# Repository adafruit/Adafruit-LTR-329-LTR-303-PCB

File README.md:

## Adafruit LTR-329 and LTR-303 Light Sensor PCBs

<a href="http://www.adafruit.com/products/5591"><br/>
Click here to purchase one from the Adafruit shop</a>

<a href="http://www.adafruit.com/products/5610"><br/>
Click here to purchase one from the Adafruit shop</a>

PCB files for the Adafruit LTR-329 and LTR-303 Light Sensor. 

Format is EagleCAD schematic and board layout
* https://www.adafruit.com/product/5591
* https://www.adafruit.com/product/5610

### Description

The Adafruit LTR-303 and LTR-329 Light Sensors are simple and popular low-cost I2C digital light sensors that are easy to integrate into your project for reliable and wide-ranging light measurements.

Perfect for a wide range of project use cases: Should we turn up the brightness of our display or dim it to save power? Which direction should your robot move to stay in an area with the most light? Is it day or night? All of these questions can be answered with the help of the LTR-303 and LTR-329. They're small, capable and inexpensive light sensors that you can include in your next project to add the detection and measurement of light.

They provide 16-bit light measurements for both Infrared and Visible+IR spectrums. Subtract one from the other to get human-visible light. Thanks to configurable gain and integration time settings, the LTR-303 can measure from 0 to 65K+ lux.

The 303 also comes with alert and IRQ capabilities so you can have a pin trigger when the reading goes above or below threshold values. Great if you want ultra-low power usage. If you don't need a version with interrupt output, check out the LTR-329 which is basically the same sensor but without the IRQ capability.

Packaged on a PCB in our STEMMA QT form factor, the LTR-303 comes integrated with a voltage regulator and level shifting circuitry to allow it to be used with 3.3V devices, like a Feather M4 or Raspberry Pi, or 5V devices, such as an Arduino. Rather than working with the itty bitty little contacts on the sensor, the PCB it's packaged on breaks out all the pins to a standard 0.1" / 2.54mm pitch header.

### License

Adafruit invests time and resources providing this open source design, please support Adafruit and open-source hardware by purchasing products from [Adafruit](https://www.adafruit.com)!

Designed by Limor Fried/Ladyada for Adafruit Industries.

Creative Commons Attribution/Share-Alike, all text above must be included in any redistribution. 
See license.txt for additional details.

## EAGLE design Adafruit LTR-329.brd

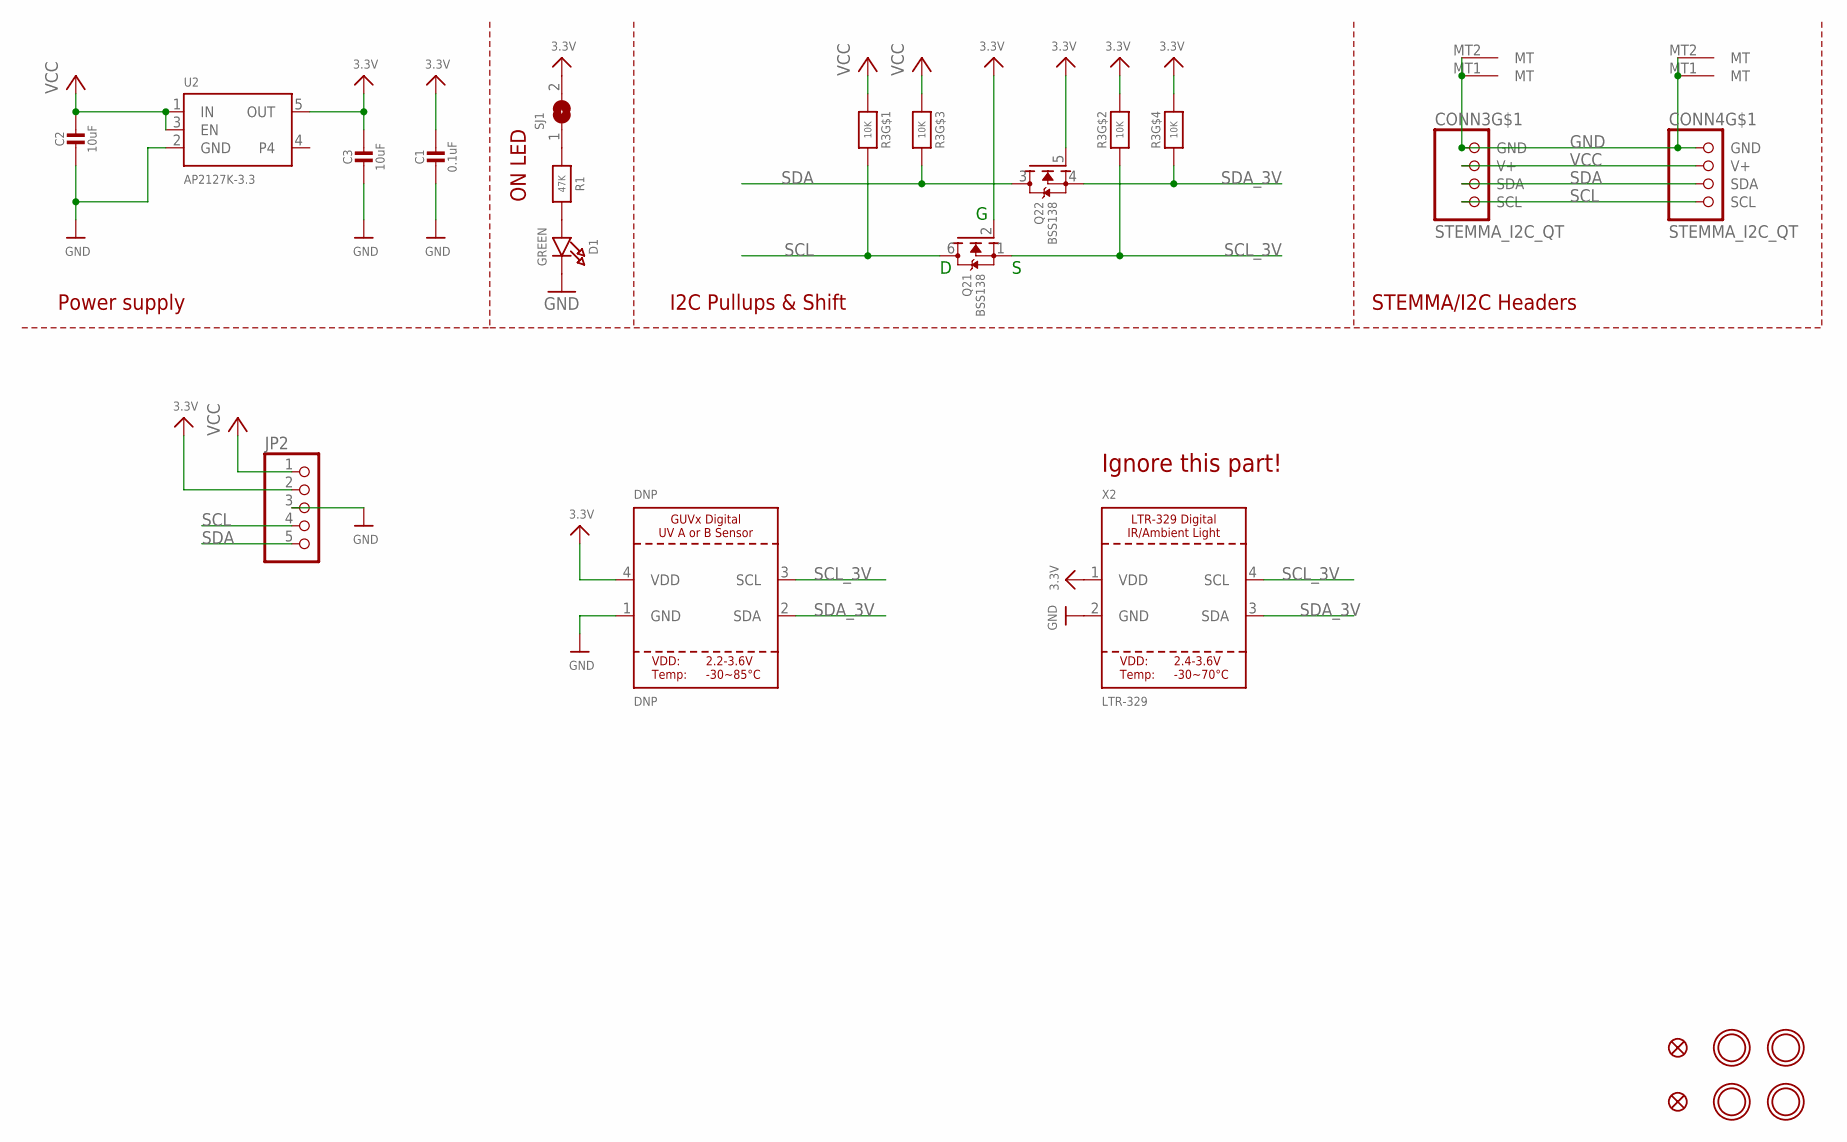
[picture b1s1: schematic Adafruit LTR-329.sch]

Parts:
C1: 0.1uF; 0603-NO
C2, C3: 10uF; 0805-NO
CONN3, CONN4: STEMMA_I2C_QT; JST_SH4
D1: GREEN; CHIPLED_0603_NOOUTLINE
DNP: DNP; GUVX_UV
FID3, FID4: FIDUCIAL_1MM
JP2: HEADER-1X570MIL; 1X05_ROUND_70
Q2: BSS138; SOT363
R1: 47K; 0603-NO
R3: 10K; RESPACK_4X0603
SJ1: SOLDERJUMPERCLOSED; SOLDERJUMPER_CLOSEDWIRE
U2: AP2127K-3.3; SOT23-5
U$1, U$17, U$19, U$21: MOUNTINGHOLE2.5; MOUNTINGHOLE_2.5_PLATED
X2: LTR-329

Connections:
3.3V: C1.1, C3.1, DNP.4 (VDD), JP2.2, Q2.2 (G), Q2.5 (G), R3.2 (1), R3.4 (1), SJ1.2, U2.5 (OUT), X2.1 (VDD)
GND: C1.2, C2.2, C3.2, CONN3.1 (GND), CONN3.MT1 (MT), CONN3.MT2 (MT), CONN4.1 (GND), CONN4.MT1 (MT), CONN4.MT2 (MT), D1.C, DNP.1 (GND), JP2.3, U2.2 (GND), X2.2 (GND)
unnamed: D1.A, R1.2
unnamed: R1.1, SJ1.1
SCL: CONN3.4 (SCL), CONN4.4 (SCL), JP2.4, Q2.6 (D), R3.8 (2)
SCL_3V: DNP.3 (SCL), Q2.1 (S), R3.7 (2), X2.4 (SCL)
SDA: CONN3.3 (SDA), CONN4.3 (SDA), JP2.5, Q2.3 (D), R3.6 (2)
SDA_3V: DNP.2 (SDA), Q2.4 (S), R3.5 (2), X2.3 (SDA)
VCC: C2.1, CONN3.2 (V+), CONN4.2 (V+), JP2.1, R3.1, R3.3 (1), U2.1 (IN), U2.3 (EN)

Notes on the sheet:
I2C Pullups & Shift
STEMMA/I2C Headers
ON LED
Power supply
Ignore this part!

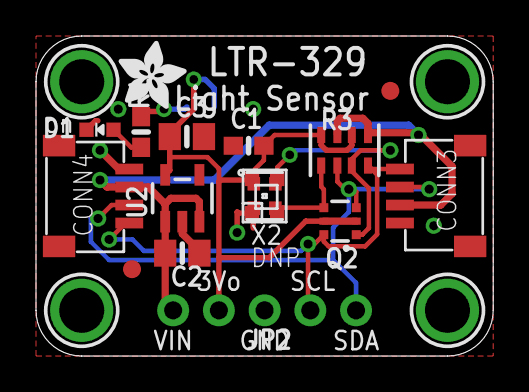
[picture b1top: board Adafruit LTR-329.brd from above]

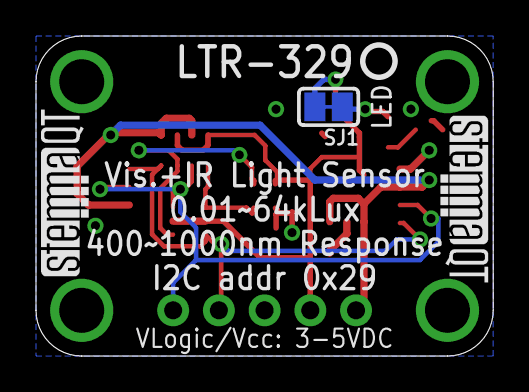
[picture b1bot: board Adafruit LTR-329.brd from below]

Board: 2 copper layers, 25.4 x 17.8 mm, 24 parts (4 on the bottom side), 9 nets.

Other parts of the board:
U$22: ADAFRUIT_3.5MM
U$25: PCBFEAT-REV-040
U$30, U$31: STEMMAQT

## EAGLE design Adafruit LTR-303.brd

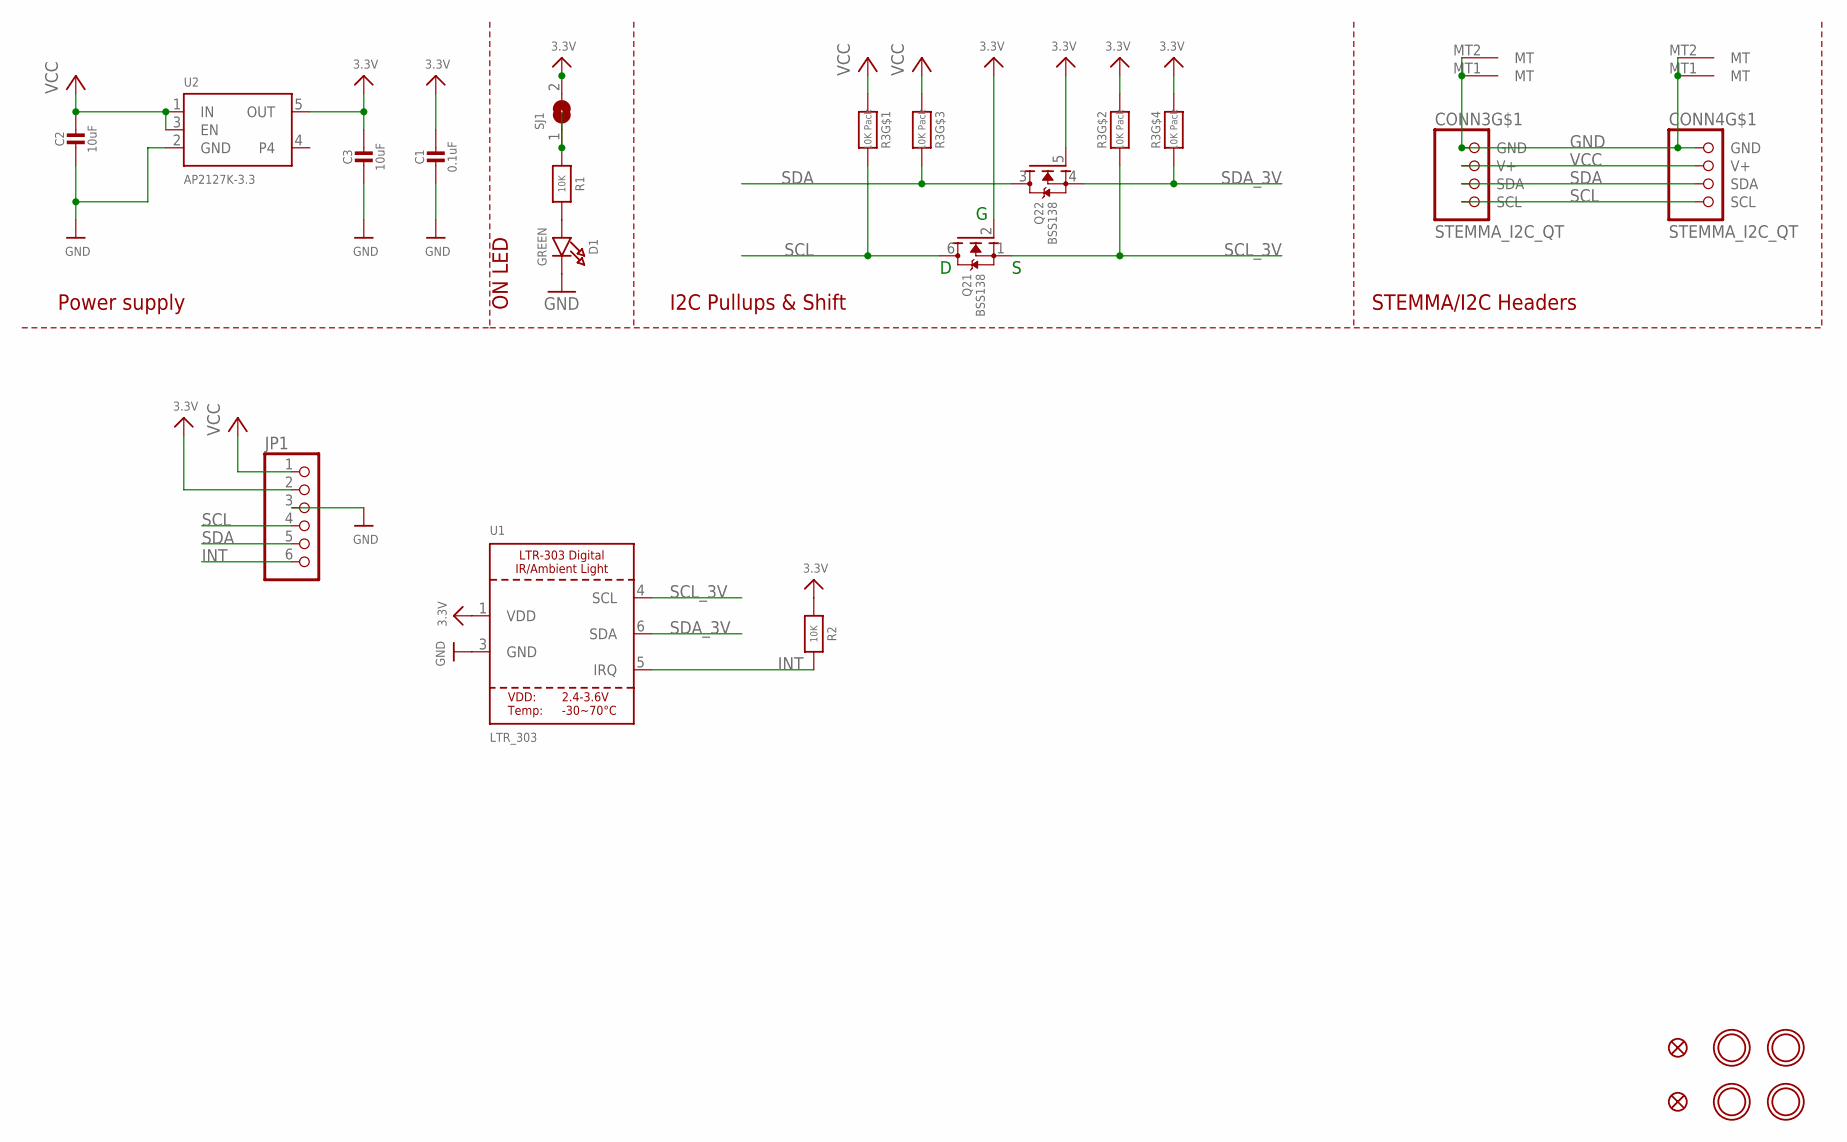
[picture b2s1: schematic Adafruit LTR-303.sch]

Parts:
C1: 0.1uF; 0603-NO
C2, C3: 10uF; 0805-NO
CONN3, CONN4: STEMMA_I2C_QT; JST_SH4
D1: GREEN; CHIPLED_0603_NOOUTLINE
FID3, FID4: FIDUCIAL_1MM
JP1: HEADER-1X670MIL; 1X06_ROUND_70
Q2: BSS138; SOT363
R1, R2: 10K; 0603-NO
R3: 10K Pack; RESPACK_4X0603
SJ1: SOLDERJUMPERCLOSED; SOLDERJUMPER_CLOSEDWIRE
U1: LTR_303; LTR390
U2: AP2127K-3.3; SOT23-5
U$1, U$17, U$19, U$21: MOUNTINGHOLE2.5; MOUNTINGHOLE_2.5_PLATED

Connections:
3.3V: C1.1, C3.1, JP1.2, Q2.2 (G), Q2.5 (G), R2.1, R3.2 (1), R3.4 (1), SJ1.2, U1.1 (VDD), U2.5 (OUT)
GND: C1.2, C2.2, C3.2, CONN3.1 (GND), CONN3.MT1 (MT), CONN3.MT2 (MT), CONN4.1 (GND), CONN4.MT1 (MT), CONN4.MT2 (MT), D1.C, JP1.3, U1.3 (GND), U2.2 (GND)
INT: JP1.6, R2.2, U1.5 (IRQ)
unnamed: D1.A, R1.2
unnamed: R1.1, SJ1.1
SCL: CONN3.4 (SCL), CONN4.4 (SCL), JP1.4, Q2.6 (D), R3.8 (2)
SCL_3V: Q2.1 (S), R3.7 (2), U1.4 (SCL)
SDA: CONN3.3 (SDA), CONN4.3 (SDA), JP1.5, Q2.3 (D), R3.6 (2)
SDA_3V: Q2.4 (S), R3.5 (2), U1.6 (SDA)
VCC: C2.1, CONN3.2 (V+), CONN4.2 (V+), JP1.1, R3.1, R3.3 (1), U2.1 (IN), U2.3 (EN)

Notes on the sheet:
I2C Pullups & Shift
STEMMA/I2C Headers
ON LED
Power supply

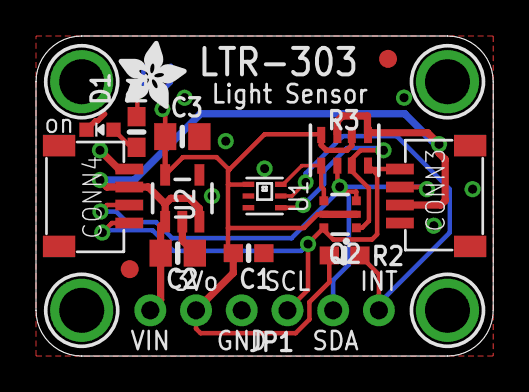
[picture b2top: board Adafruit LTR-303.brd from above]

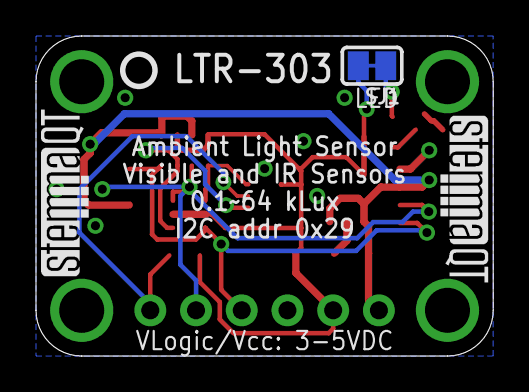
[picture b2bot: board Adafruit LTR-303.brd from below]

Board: 2 copper layers, 25.4 x 17.8 mm, 24 parts (4 on the bottom side), 10 nets.

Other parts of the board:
U$22: ADAFRUIT_3.5MM
U$25: PCBFEAT-REV-040
U$30, U$31: STEMMAQT

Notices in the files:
parts and their libraries:
microbuilder: This work is placed in the public domain, and may be freely used for commercial and non-commercial work with the following conditions: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
